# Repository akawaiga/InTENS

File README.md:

# InTENS project

# Overview
The InTENS is a high-frequency and high-intensity nerve stimulation
treatment for pain management. This project builds on prior research
from Boston Univesity's EDF and Bridge BUilders program, guided by a
physician, and is supplemented by phantom model testing and a new
electrode design.

# Features
*   single-channel system for compactness
*   delivers sine waves instead of commercial TENS pulse for user comfort
*   capable of delivering frequecnies up of atleast 1kHz
*   capable of delivering high-intensity waves of up to 140 Vpp

# Changes required to the board before use:

*   Solder a wire between pins 1 and 6 of U1 (best done on the bottom side)
This connects DAC reference to 5V
*   Solder a wire between J4 pin 3 and J2 pin 5
*   Solder a wire between J4 pin 4 and J2 pin 7
This connects the SPI data and clock to the right Arduino pins
*   addd a 100kohm resistor to R5 as 2mA is the reccommended ouptut current (for saftey)(ArduinoSheild PCB) 
*   addd a 100kohm resistor to C4 and C6 to reduce load on DC DC conversrters so both can function at same time (Battery PCB) 
*   heat sink reccommended on the 5V regulator (U1 on BatteryPCB) 

# User Interface 
Installation of Arduino IDE and Packages

* IDE download - https://www.arduino.cc/en/software
* Pathway to DAC MCP Package - https://github.com/akawaiga/InTENS/tree/main/Arduino 

Setup

*  Start Arduino IDE and connect the InTens device to the laptop. Ensure the correct board and output port are selected within the IDE. 
*  Ensure the DAC MCP library is downloaded from the GitHub repository
*  Set output baud rate to 11500
*  Upload the code to the Arduino and turn on both switches

Controlling Frequency and Amplitude

*   The initial frequency can be set using the freq variable. 
*   The initial amplitude can be set using the desiredAmplitude variable. 
*   The increment for the frequency can be set by changing the integer
  value in code line “freq+=10” and “freq-=10”.
*   The increment for the amplitude can be set by changing the integer
  value in code line “desiredAmplitude+=10” and
  “desiredAmplitude-=10”.
*   The frequency can be increased by entering “+” in the Arduino IDE.
*   The frequency can be decreased by entering “-” in the Arduino IDE.
*   The amplitude can be increased by entering “A” in the Arduino IDE. 
*   The amplitude can be decreased by entering “a” in the Arduino IDE. 

Note: 

You can compound your increments by adding multiple inputs at
once. For example: “+++++” or “AAAA”. Avoid combining inputs such as
“AaA”.

The code currently does not support decimal point increments (float),
please use integers such as “1” or “25”.

# Conclusion
Though with 2 PCBs we have acheived the orginal goal of creating a
TENS device capcable of creating a sine wave, >1kHz frequecny, and
140Vpp amplitude, we recommend the following updates to the next
iteration of the device:

*   Shaft Encoder:incorporate a knob to manually control frequency and
  amplitude rather than through the IDE. This has been done in
  previous versions of the device (2021-22)
*   LCD Display:incorporate LCD display to show output frequency and
  amplitude and various parameter changes when changing parameters
  using the knob.
*   Float type increments: currently the code uses type int for the
  amplitude and frequency variables, update this to type float to
  allow decimal increments.
*   Safety: consult with electrical engineers to build in further safety
  features to ensure the device does not provide unwanted currents to
  the patient.
*   Finger Clamp: update the finger clamp design to include jaws
  (example a claw hair clip) so it can accommodate smaller patient
  anatomies.
*   Phantom Testing: continue developing a phantom model for the finger
  to demonstrate safety and efficacy.

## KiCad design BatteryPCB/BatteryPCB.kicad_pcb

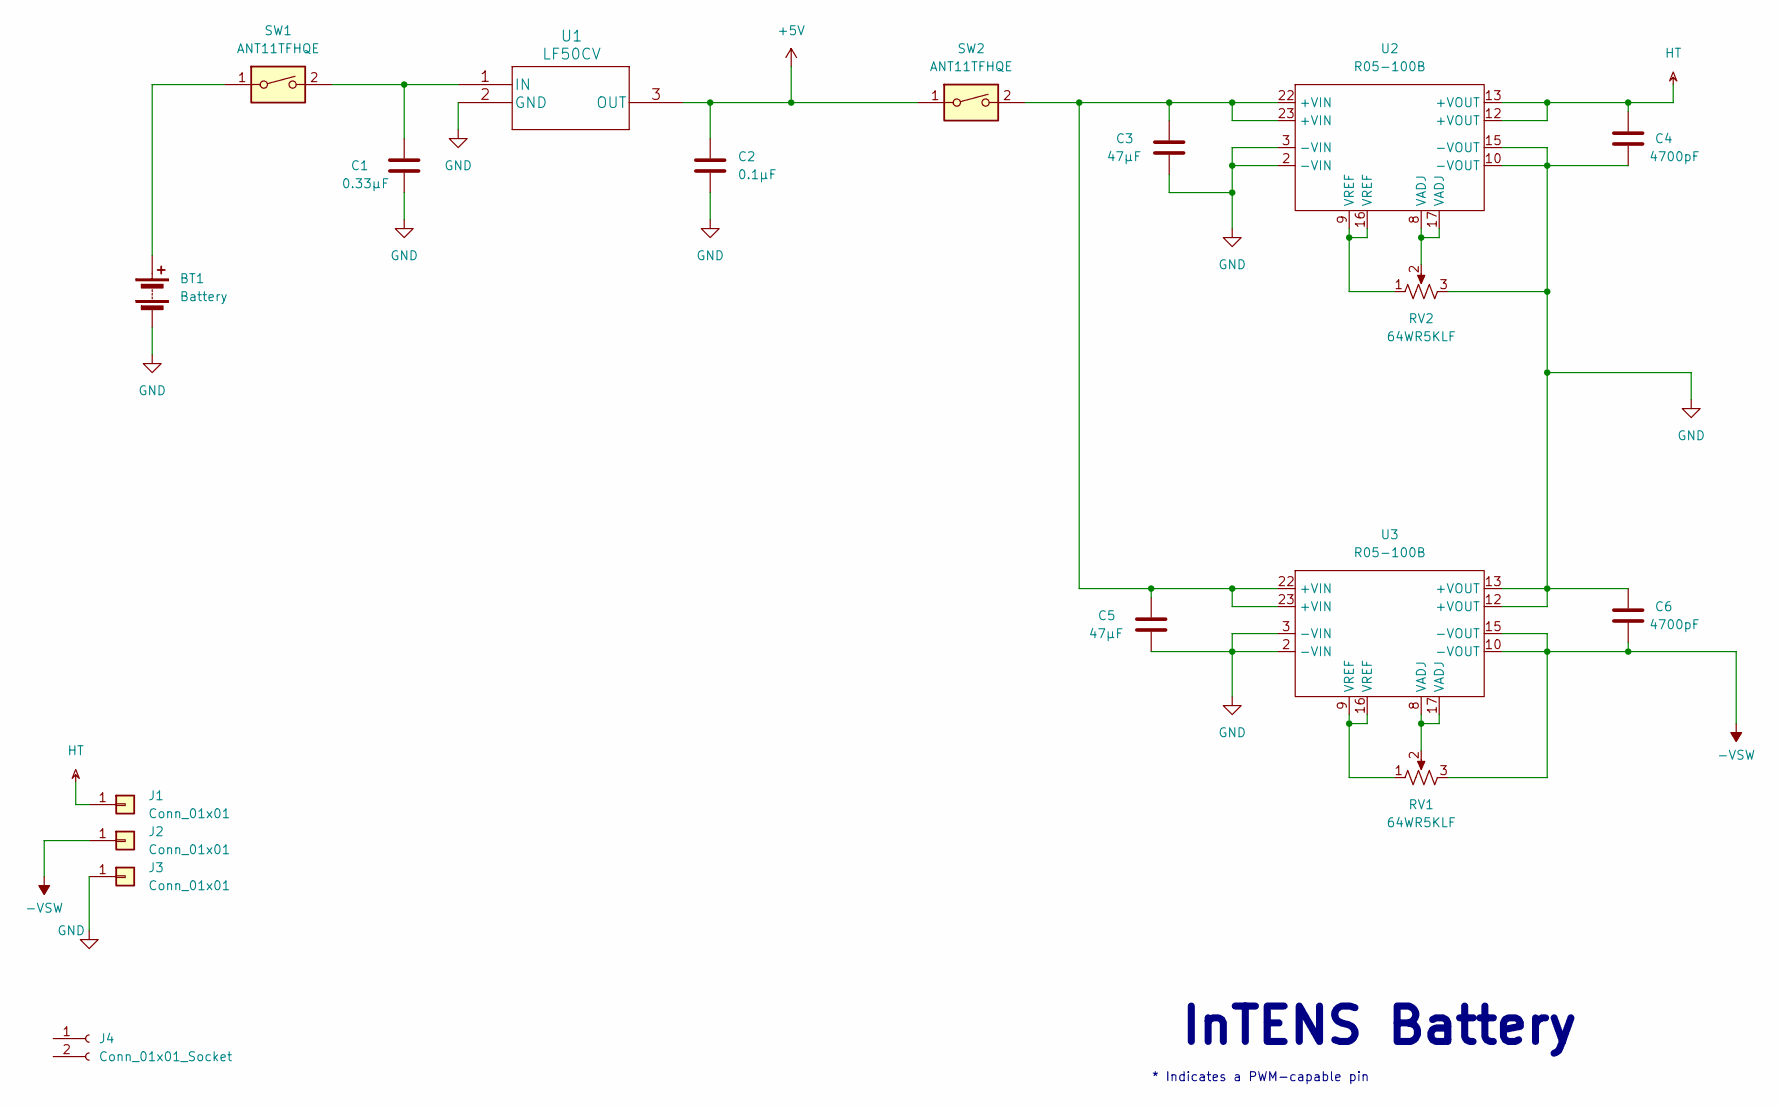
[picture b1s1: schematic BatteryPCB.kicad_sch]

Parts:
BT1: Battery; CON_39296028
C1: 0.33μF; C_Rect_L4.6mm_W2.0mm_P2.50mm_MKS02_FKP02
C2: 0.1μF; C_Rect_L4.6mm_W2.0mm_P2.50mm_MKS02_FKP02
C3, C5: 47μF; C_1206_3216Metric_Pad1.33x1.80mm_HandSolder
C4, C6: 4700pF; C_1206_3216Metric_Pad1.33x1.80mm_HandSolder
J1, J2, J3: Conn_01x01; Pin_D1.0mm_L10.0mm
J4: Conn_01x01_Socket; PinSocket_1x02_P2.54mm_Vertical
RV1, RV2: 64WR5KLF; RES3_64W_TTE
SW1, SW2: ANT11TFHQE; 100SP1T1_EWI
U1: LF50CV
U2, U3: R05-100B; DIP-24_W15.24mm

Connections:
+5V: C2.1, SW2.1, U1.3 (OUT)
-VSW: C6.1, J2.1, RV1.3, U3.10 (-VOUT), U3.15 (-VOUT)
GND: BT1.2 (-), C1.2, C2.2, C3.1, C4.1, C5.1, C6.2, J3.1, RV2.3, U1.2 (GND), U2.2 (-VIN), U2.3 (-VIN), U2.10 (-VOUT), U2.15 (-VOUT), U3.2 (-VIN), U3.3 (-VIN), U3.12 (+VOUT), U3.13 (+VOUT)
HT: C4.2, J1.1, U2.12 (+VOUT), U2.13 (+VOUT)
unnamed: BT1.1 (+), SW1.1
unnamed: C3.2, C5.2, SW2.2, U2.22 (+VIN), U2.23 (+VIN), U3.22 (+VIN), U3.23 (+VIN)
unnamed: RV1.1, U3.9 (VREF), U3.16 (VREF)
unnamed: RV1.2, U3.8 (VADJ), U3.17 (VADJ)
unnamed: RV2.1, U2.9 (VREF), U2.16 (VREF)
unnamed: RV2.2, U2.8 (VADJ), U2.17 (VADJ)
unnamed: C1.1, SW1.2, U1.1 (IN)

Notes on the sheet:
InTENS Battery
* Indicates a PWM-capable pin

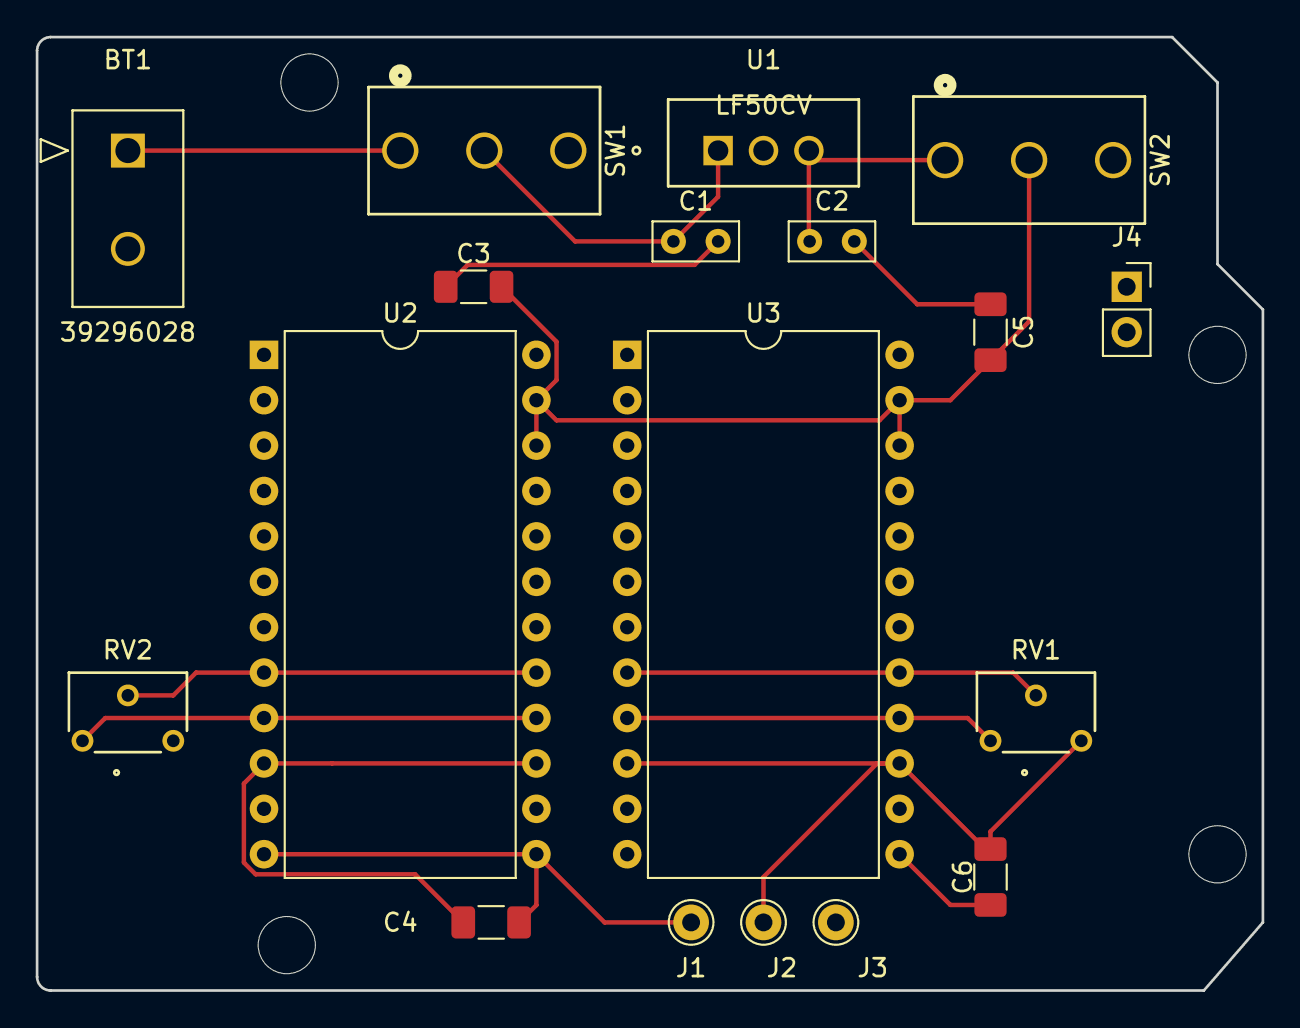
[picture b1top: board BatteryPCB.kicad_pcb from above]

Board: 2 copper layers, 68.6 x 53.3 mm, 22 parts (0 on the bottom side), 11 nets.

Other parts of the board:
MH1, MH2, MH3, MH4: MountingHole_3.2mm

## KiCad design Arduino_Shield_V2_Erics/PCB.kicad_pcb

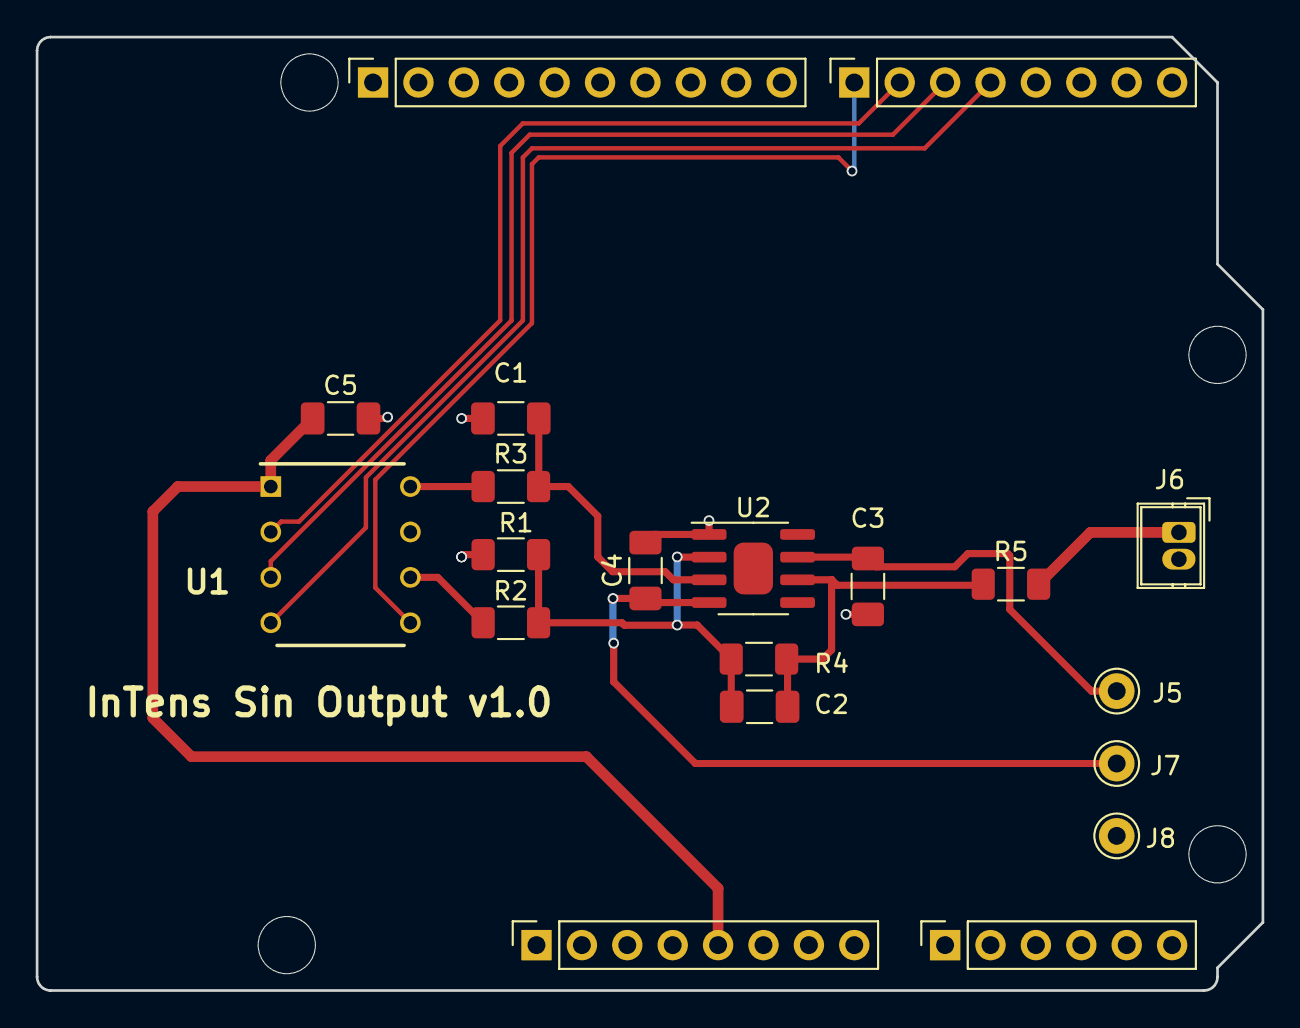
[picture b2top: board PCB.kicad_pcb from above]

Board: 2 copper layers, 68.6 x 53.3 mm, 24 parts (0 on the bottom side), 15 nets.

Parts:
C1: 470pF; C_1206_3216Metric_Pad1.33x1.80mm_HandSolder
C2: 10pF; C_1206_3216Metric_Pad1.33x1.80mm_HandSolder
C3, C4: 0.1uF; C_1206_3216Metric_Pad1.33x1.80mm_HandSolder
C5: 0.1 uF; C_1206_3216Metric_Pad1.33x1.80mm_HandSolder
J1: Power; PinSocket_1x08_P2.54mm_Vertical
J2: Digital/PWM; PinSocket_1x10_P2.54mm_Vertical
J3: Analog; PinSocket_1x06_P2.54mm_Vertical
J4: Digital/PWM; PinSocket_1x08_P2.54mm_Vertical
J5, J7, J8: Conn_01x01; Pin_D1.0mm_L10.0mm
J6: Conn_01x01_Socket; Wuerth_WR-WTB_64800211622_1x02_P1.50mm_Vertical
MH1, MH2, MH3, MH4: MountingHole_3.2mm
R1: 16.2kΩ; R_1206_3216Metric_Pad1.30x1.75mm_HandSolder
R2: 16.9kΩ; R_1206_3216Metric_Pad1.30x1.75mm_HandSolder
R3: 10kΩ; R_1206_3216Metric_Pad1.30x1.75mm_HandSolder
R4: 453kΩ; R_1206_3216Metric_Pad1.30x1.75mm_HandSolder
R5: 40kΩ; R_1206_3216Metric_Pad1.30x1.75mm_HandSolder
U1: MCP4921; DIP781W56P254L950H533Q8N
U2: LTC6090; SOIC-8-1EP_3.9x4.9mm_P1.27mm_EP2.29x3mm

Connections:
+5V: C5.1, J1.5, U1.1 (Vdd)
-VSW: C4.1, J7.1, U2.4
/4: J4.4, U1.4 (SDI)
/7: J4.1, U1.5 (~LDAC)
/*5: J4.3, U1.3 (SCK)
/*6: J4.2, U1.2 (~CS)
GND: C1.2, C3.2, C4.2, C5.2, J1.6, J1.7, J2.4, J6.2, J8.1, R2.1, U1.7 (Vss), U2.1
HT: C3.1, J5.1, U2.7
unnamed: C1.1, R3.2, U2.3
unnamed: C2.1, R1.1, R2.2, R4.1, U2.2
unnamed: C2.2, R4.2, R5.1, U2.6
unnamed: J6.1, R5.2
unnamed: R3.1, U1.8 (Vout)
unnamed: R1.2, U1.6 (Vref)
unnamed: U2.5, U2.8

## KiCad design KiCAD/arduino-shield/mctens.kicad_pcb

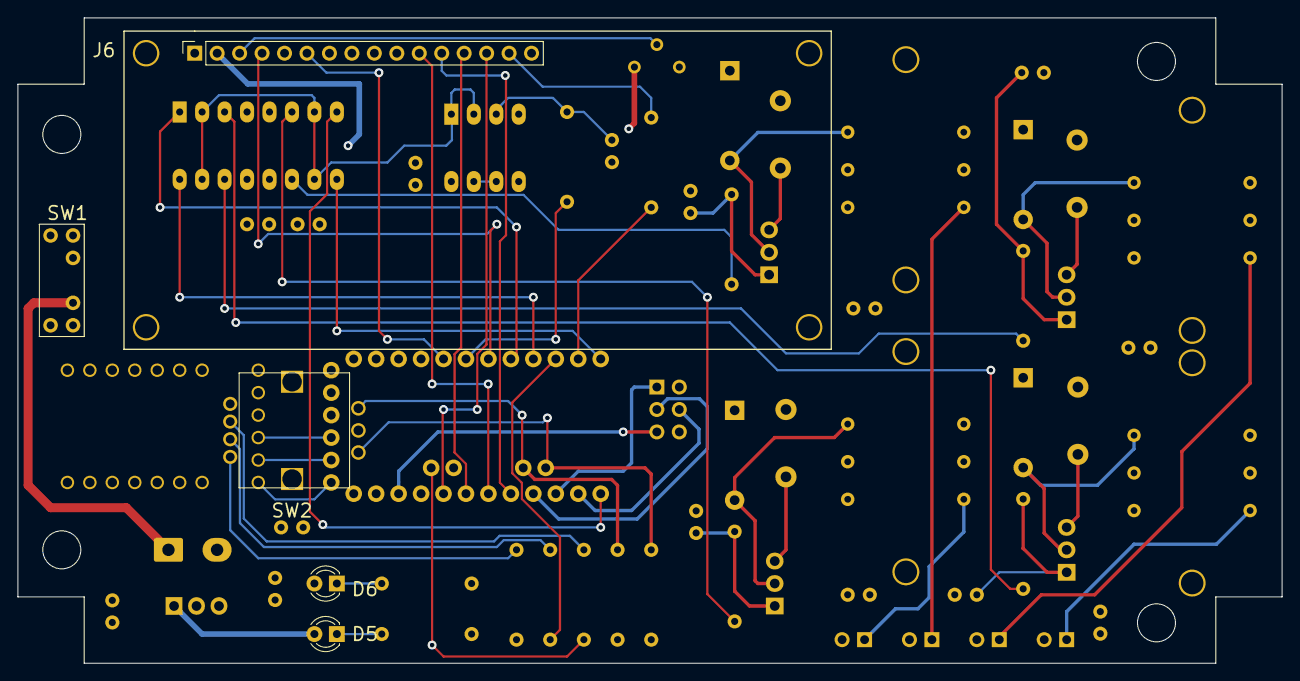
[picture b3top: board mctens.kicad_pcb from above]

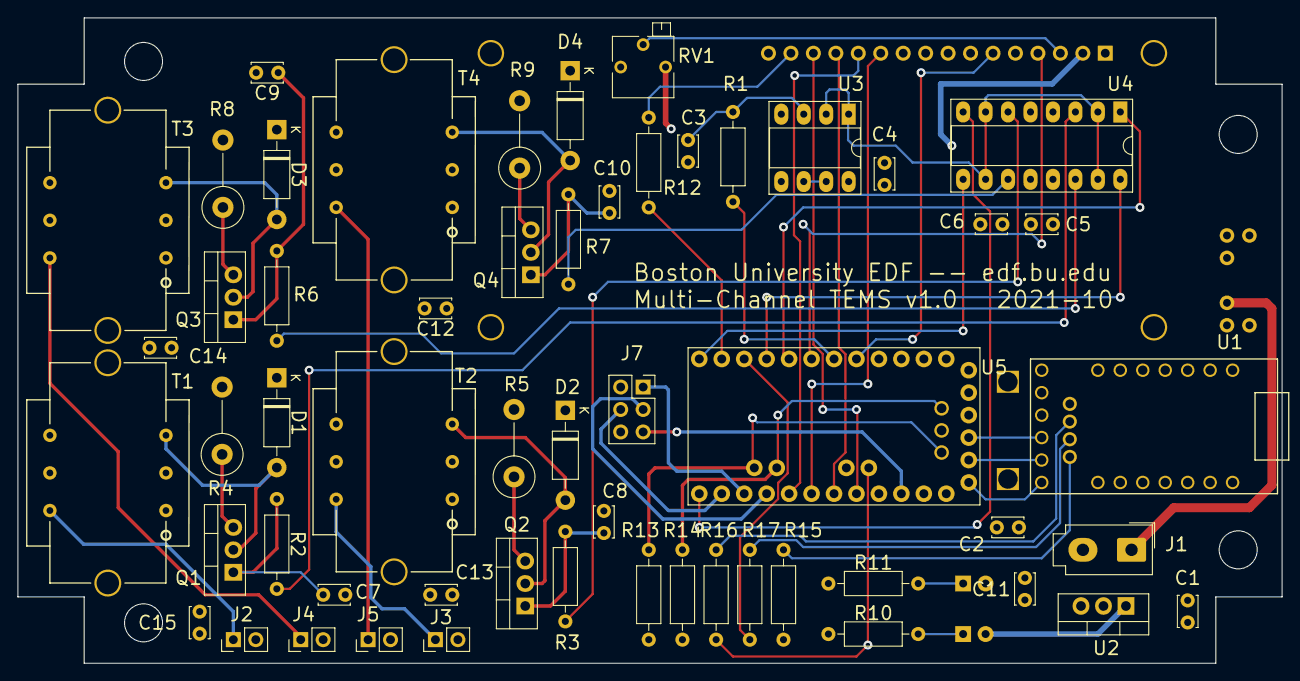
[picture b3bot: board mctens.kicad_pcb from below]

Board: 4 copper layers, 143.0 x 73.0 mm, 65 parts (56 on the bottom side), 57 nets.

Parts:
C1, C2, C4, C5, C6, C11: 0.1uF; C_Disc_D3.4mm_W2.1mm_P2.50mm
C3, C12, C13, C14, C15: 1uF; C_Disc_D3.4mm_W2.1mm_P2.50mm
C7, C8, C9, C10: OMIT; C_Disc_D3.4mm_W2.1mm_P2.50mm
D1, D2, D3, D4: 1N4005; D_DO-41_SOD81_P10.16mm_Horizontal
D5, D6: LED; LED_D3.0mm
H1, H2, H3, H4: MountingHole; MountingHole_4.3mm_M4
J1: Conn_01x02; Molex_Mini-Fit_Jr_5566-02A_2x01_P4.20mm_Vertical
J2, J3, J4, J5: CONN; PinHeader_1x02_P2.54mm_Vertical
J6: Conn_01x16; LCD_module_3D
J7: Conn_02x03_Odd_Even; PinSocket_2x03_P2.54mm_Vertical
Q1, Q2, Q3, Q4: FQP19N20C; TO-220-3_Vertical
R1, R2, R3, R6, R7: 100; R_Axial_DIN0207_L6.3mm_D2.5mm_P10.16mm_Horizontal
R4, R5, R8, R9: 8R2 2W; R_Axial_DIN0414_L11.9mm_D4.5mm_P7.62mm_Vertical
R10, R13, R14, R15: 10k; R_Axial_DIN0207_L6.3mm_D2.5mm_P10.16mm_Horizontal
R11, R16, R17: 2k; R_Axial_DIN0207_L6.3mm_D2.5mm_P10.16mm_Horizontal
R12: 1k; R_Axial_DIN0207_L6.3mm_D2.5mm_P10.16mm_Horizontal
RV1: 5K; Potentiometer_Bourns_3266P_Horizontal
SW1: SW_SPST; SW-A11AB-3D
SW2: COM-15140; rotary-RG-3D
T1, T2, T3, T4: Transformer_1P_1S; 42TL-transformer-v2
U1: FT231X_breakout
U2: 12V_3.3V_DC; TO-220-3_Vertical
U3: LM358; DIP-8_W7.62mm_Socket_LongPads
U4: MAX4678; DIP-16_W7.62mm_Socket_LongPads
U5: ARDUINO_PRO_MINI; MODULE_ARDUINO_PRO_MINI_3D

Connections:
+3V3: C2.1, C6.1, C11.1, D6.2, J6.2, J7.2, R13.1, R14.1, R15.1, RV1.1, U2.3, U4.12, U5.JP1_4
+12V: C1.1, C4.1, C5.1, C12.1, C13.1, C14.1, C15.1, D1.1, D2.1, D3.1, D4.1, D5.2, SW1.2, T1.1, T2.1, T3.1, T4.1, U2.1, U3.8, U4.13
/DRV4: U4.8, U5.JP6_12
/DTR: U1.C6, U5.JP1_1
/KNOB_A: R13.2, SW2.A, U5.JP3_1
/KNOB_B: R14.2, SW2.B, U5.JP3_2
/KNOB_G: R17.1, U5.JP7_3
/KNOB_R: R16.1, U5.JP2_2
/LCD_D4: J6.11, U5.JP6_7
/LCD_D5: J6.12, U5.JP6_8
/LCD_D6: J6.13, U5.JP6_6
/LCD_D7: J6.14, U5.JP6_5
/LCD_E: J6.6, U5.JP7_8
/LCD_LIGHT: R12.2, U5.JP7_2
/LCD_RS: J6.4, U5.JP7_6
/RXI: U1.C4, U5.JP1_3
/TXO: U1.C5, U5.JP1_2
GND: C1.2, C2.2, C3.2, C4.2, C5.2, C6.2, C7.2, C8.2, C9.2, C10.2, C11.2, C12.2, C13.2, C14.2, C15.2, J1.2, J2.2, J3.2, J4.2, J5.2, J6.1, J6.5, J6.16, J7.6, R4.2, R5.2, R8.2, R9.2, R10.1, R11.1, RV1.3, SW2.1, SW2.C, T1.4, T1.7, T1.8, T2.4, T2.7, T2.8, T3.4, T3.7, T3.8, T4.4, T4.7, T4.8, U1.A7, U1.C1, U1.C2, U2.2, U3.4, U3.5, U4.4, U4.5, U5.JP1_5, U5.JP1_6, U5.JP6_2, U5.JP7_9
unnamed: C3.1, R1.1, U3.3
unnamed: C7.1, Q1.1, R2.1
unnamed: C8.1, Q2.1, R3.1
unnamed: C9.1, Q3.1, R6.1
unnamed: C10.1, Q4.1, R7.1
unnamed: D1.2, Q1.2, T1.3
unnamed: D2.2, Q2.2, T2.3
unnamed: D3.2, Q3.2, T3.3
unnamed: D4.2, Q4.2, T4.3
unnamed: D5.1, R10.2
unnamed: D6.1, R11.2
unnamed: J1.1, SW1.1
unnamed: J2.1, T1.6
unnamed: J3.1, T2.6
unnamed: J4.1, T3.6
unnamed: J5.1, T4.6
unnamed: J6.3, RV1.2
unnamed: J6.15, R12.1
unnamed: J7.1, U5.JP6_10
unnamed: J7.3, U5.JP6_9
unnamed: J7.4, U5.JP6_11
unnamed: J7.5, U5.JP6_3
unnamed: Q1.3, R4.1
unnamed: Q2.3, R5.1
unnamed: Q3.3, R8.1
unnamed: Q4.3, R9.1
unnamed: R1.2, U5.JP7_7
unnamed: R2.2, U4.3
unnamed: R3.2, U4.6
unnamed: R6.2, U4.14
unnamed: R7.2, U4.11
unnamed: R15.2, SW2.4
unnamed: R16.2, SW2.2
unnamed: R17.2, SW2.3
unnamed: U3.1, U3.2, U4.2, U4.7, U4.10, U4.15
unnamed: U3.6, U3.7
unnamed: U4.1, U5.JP7_5
unnamed: U4.9, U5.JP7_1
unnamed: U4.16, U5.JP7_4

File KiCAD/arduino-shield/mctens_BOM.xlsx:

Please order for two boards plus 1 spare of each IC and round up on the passive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
Reference | Qty/Board | Value | Footprint | CatNo | Vendor | QQ | Project
BT1 BT2 | 2 | Battery_Holder |  | 36-2478-ND | DigiKey |  | MULTI-TEMS
C3 | 1 | 1uF | Capacitor_THT:C_Disc_D3.4mm_W2.1mm_P2.50mm | 399-14394-1-ND | DigiKey |  | MULTI-TEMS
C1 C2 C4 C5 C6 C11 | 6 | 0.1uF | Capacitor_THT:C_Disc_D3.4mm_W2.1mm_P2.50mm | 399-9859-2-ND | DigiKey |  | MULTI-TEMS
C7 C8 C9 C10 | 4 | OMIT | Capacitor_THT:C_Disc_D3.4mm_W2.1mm_P2.50mm | OMIT
D1 D2 D3 D4 | 4 | 1N4005 | Diode_THT:D_DO-41_SOD81_P10.16mm_Horizontal | 1N4007-TPMSCT-ND | DigiKey |  | MULTI-TEMS
D5 D6 | 2 | LED | LED_THT:LED_D3.0mm | 1497-XLMDK65D-ND | DigiKey |  | MULTI-TEMS
H1 H2 H3 H4 | 4 | MountingHole | MountingHole:MountingHole_4.3mm_M4 | OMIT
J1 | 1 | Conn_01x02 | Connector_Molex:Molex_Mini-Fit_Jr_5566-02A_2x01_P4.20mm_Vertical | WM23820-ND | DigiKey |  | MULTI-TEMS
J2 J3 J4 J5 | 4 | CONN | Connector_PinHeader_2.54mm:PinHeader_1x02_P2.54mm_Vertical | S1011EC-02-ND | DigiKey |  | MULTI-TEMS
J6 | 1 | Conn_01x16 | Connector_PinHeader_2.54mm:PinHeader_1x16_P2.54mm_Vertical | 2057-PH1-16-UA-ND | DigiKey |  | MULTI-TEMS
N1 | 1 | Enclosure_1591DSBK |  | HM105-ND | DigiKey |  | MULTI-TEMS
Q1 Q2 Q3 Q4 | 4 | FQP19N20C | Package_TO_SOT_THT:TO-220-3_Vertical | FQP19N20C-ND | DigiKey |  | MULTI-TEMS
R12 | 1 | 1k | Resistor_THT:R_Axial_DIN0207_L6.3mm_D2.5mm_P10.16mm_Horizontal | Generic 1k ohm 1/4W | DigiKey |  | MULTI-TEMS
R10 R13 R14 R15 | 4 | 10k | Resistor_THT:R_Axial_DIN0207_L6.3mm_D2.5mm_P10.16mm_Horizontal | Generic 10k ohm 1/4W | DigiKey |  | MULTI-TEMS
R11 R16 R17 | 3 | 2k | Resistor_THT:R_Axial_DIN0207_L6.3mm_D2.5mm_P10.16mm_Horizontal | Generic 2k ohm 1/4W | DigiKey |  | MULTI-TEMS
R1 R2 R3 R6 R7 | 5 | 100 | Resistor_THT:R_Axial_DIN0207_L6.3mm_D2.5mm_P10.16mm_Horizontal | Generic 100 ohm 1/4W | DigiKey |  | MULTI-TEMS
R4 R5 R8 R9 | 4 | 8R2 2W | Resistor_THT:R_Axial_DIN0414_L11.9mm_D4.5mm_P20.32mm_Horizontal | 8.2 ohm 2W | DigiKey |  | MULTI-TEMS
RV1 | 1 | 5K | Potentiometer_THT:Potentiometer_Bourns_3266P_Horizontal | 3266P-1-502LF-ND | DigiKey |  | MULTI-TEMS
SW1 | 1 | SW_SPST | arduino-shield:SW-A11AB | 360-3868-ND | DigiKey |  | MULTI-TEMS
SW2 | 1 | COM-15140 | arduino-shield:rotary-RG | OMIT
T1 T2 T3 T4 | 4 | Transformer_1P_1S | arduino-shield:42TL-transformer | OMIT - customer
U2 | 1 | 12V_3.3V_DC | Package_TO_SOT_THT:TO-220-3_Vertical | 1951-TSR1.5-2433E-ND | DigiKey |  | MULTI-TEMS
U3 | 1 | LM358 | Package_DIP:DIP-8_W7.62mm_Socket_LongPads | LM2904NNS/NOPB-ND | DigiKey |  | MULTI-TEMS
U4 | 1 | MAX4678 | Package_DIP:DIP-16_W7.62mm_Socket_LongPads | MAX4678EPE+-ND | DigiKey |  | MULTI-TEMS
U5 | 1 | ARDUINO_PRO_MINI | arduino-shield:MODULE_ARDUINO_PRO_MINI
XX1 | 4 | 2 Pin Housing |  | WM2800 | DigiKey | 4 | MULTI-TEMS
XX2 | 8 | Crimp Pins |  | WM2513 | DigiKey | 8 | MULTI-TEMS
XX3 | 4 | 3.5 mm jack |  | 839-1410-ND | DigiKey | 4 | MULTI-TEMS
XX4 | 4 | 3.5 mm cable |  | 839-1033-ND | DigiKey | 4 | MULTI-TEMS
XX5 | 4 | 16 pin socket |  | 929850-01-16-ND | DigiKey | 4 | MULTI-TEMS

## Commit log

2024-02-05 copy over multi-channel and initial sine wave design
2024-02-20 Add files via upload
    This is the design we have for now, we will run the simulations now and tweak the values accordingly.
2024-02-21 Add files via upload
    Arduino Shield for Sine-Output TENS
2024-02-21 Add files via upload
    InTENS Arduino Shield Folder
2024-02-21 Attempt to restore project
2024-02-22 Initial comments
2024-02-22 Serious edits during 2/22 meeting by Eric
2024-02-25 fixed scematic wiring, PCB tracks, checked footprint dimensions, and added 3D models
2024-03-04 Updated PCB (correct orientation)
2024-03-04 semi-updated from Eric 3/4 notes
2024-03-04 updated PCB from 3/4 Eric Meeting
2024-03-05 ERIC: Add part numbers to symbols for ordering
2024-03-05 ERIC: generate V1 gerbers with GND fixed
2024-03-05 Eric's version of layout
2024-03-27 Create ArduinoCode
    code for InTENS Device
2024-03-27 first version software
2024-03-27 Add (working) Arduino example code
2024-03-28 Add files via upload
    PCB Board for battery
2024-03-29 Updates from 3/29 comments
2024-03-30 In progress changes from 3/29 2nd comments
2024-03-30 Update README.md
    3/29 Eric Notes
2024-03-30 2nd Updates from 3/29 Comments
2024-03-30 2nd Update from 3/29 comments
2024-03-31 Updated from 3/30 comments
2024-03-31 Update README.md
    3/30 Eric notes for 2/29 updated Battery PCB
2024-04-01 4/1 trim pot change
2024-04-01 4/1 trim pot change + gerber files
2024-04-15 Working code for freq and amp input
2024-04-15 Working code for freq and amp
2024-04-18 code from 3/18
2024-04-19 Add files via upload
    4/19 working amp and freq
2024-05-16 Add files via upload
    Electrode + housing CAD designs
2026-04-16 readme

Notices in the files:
parts and their libraries:
Copyright 2016 Accelerated Designs. All rights reserved.
